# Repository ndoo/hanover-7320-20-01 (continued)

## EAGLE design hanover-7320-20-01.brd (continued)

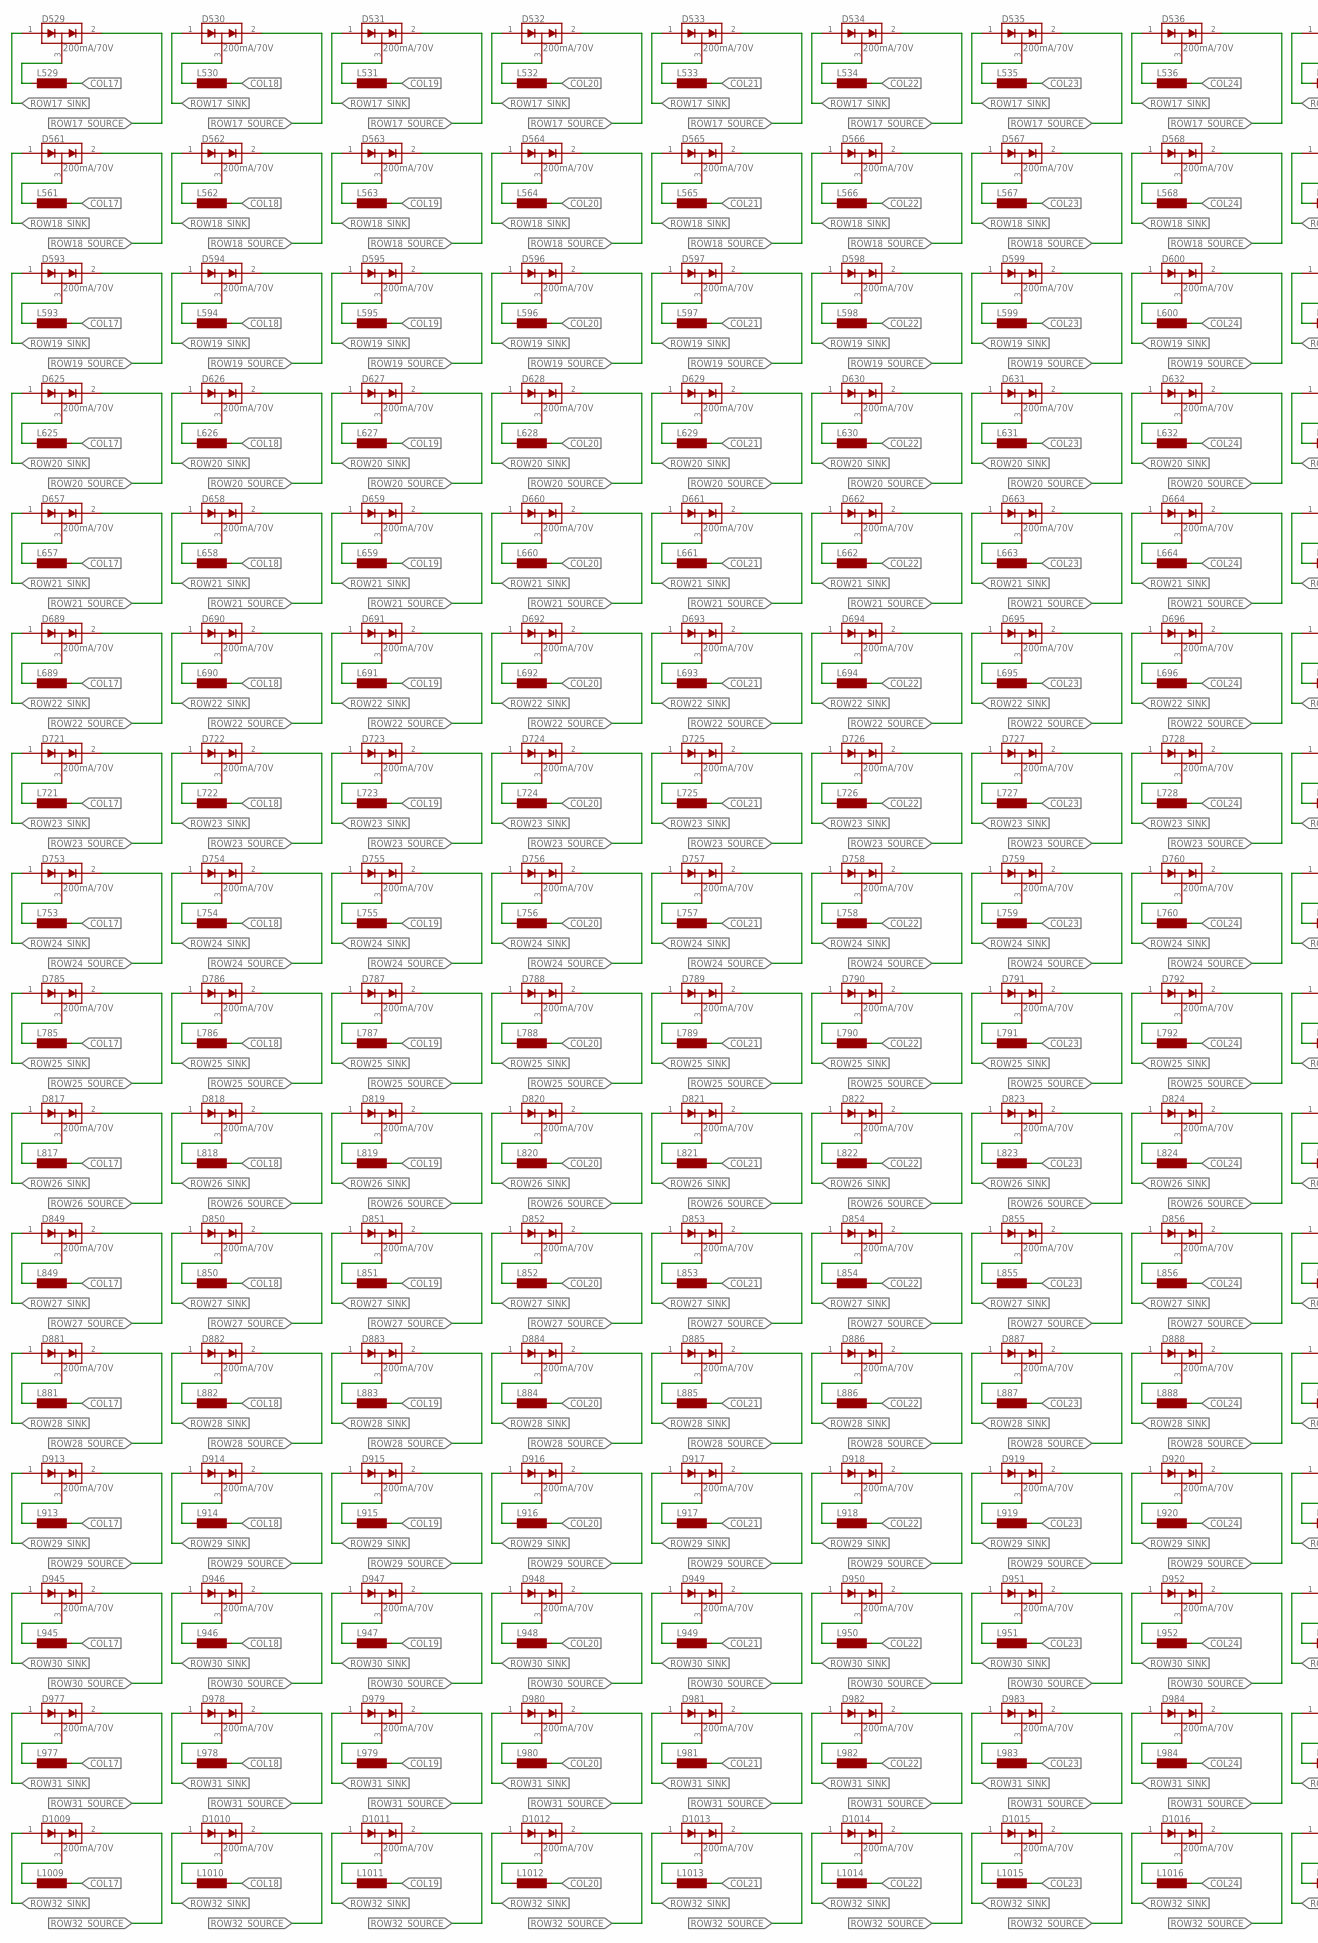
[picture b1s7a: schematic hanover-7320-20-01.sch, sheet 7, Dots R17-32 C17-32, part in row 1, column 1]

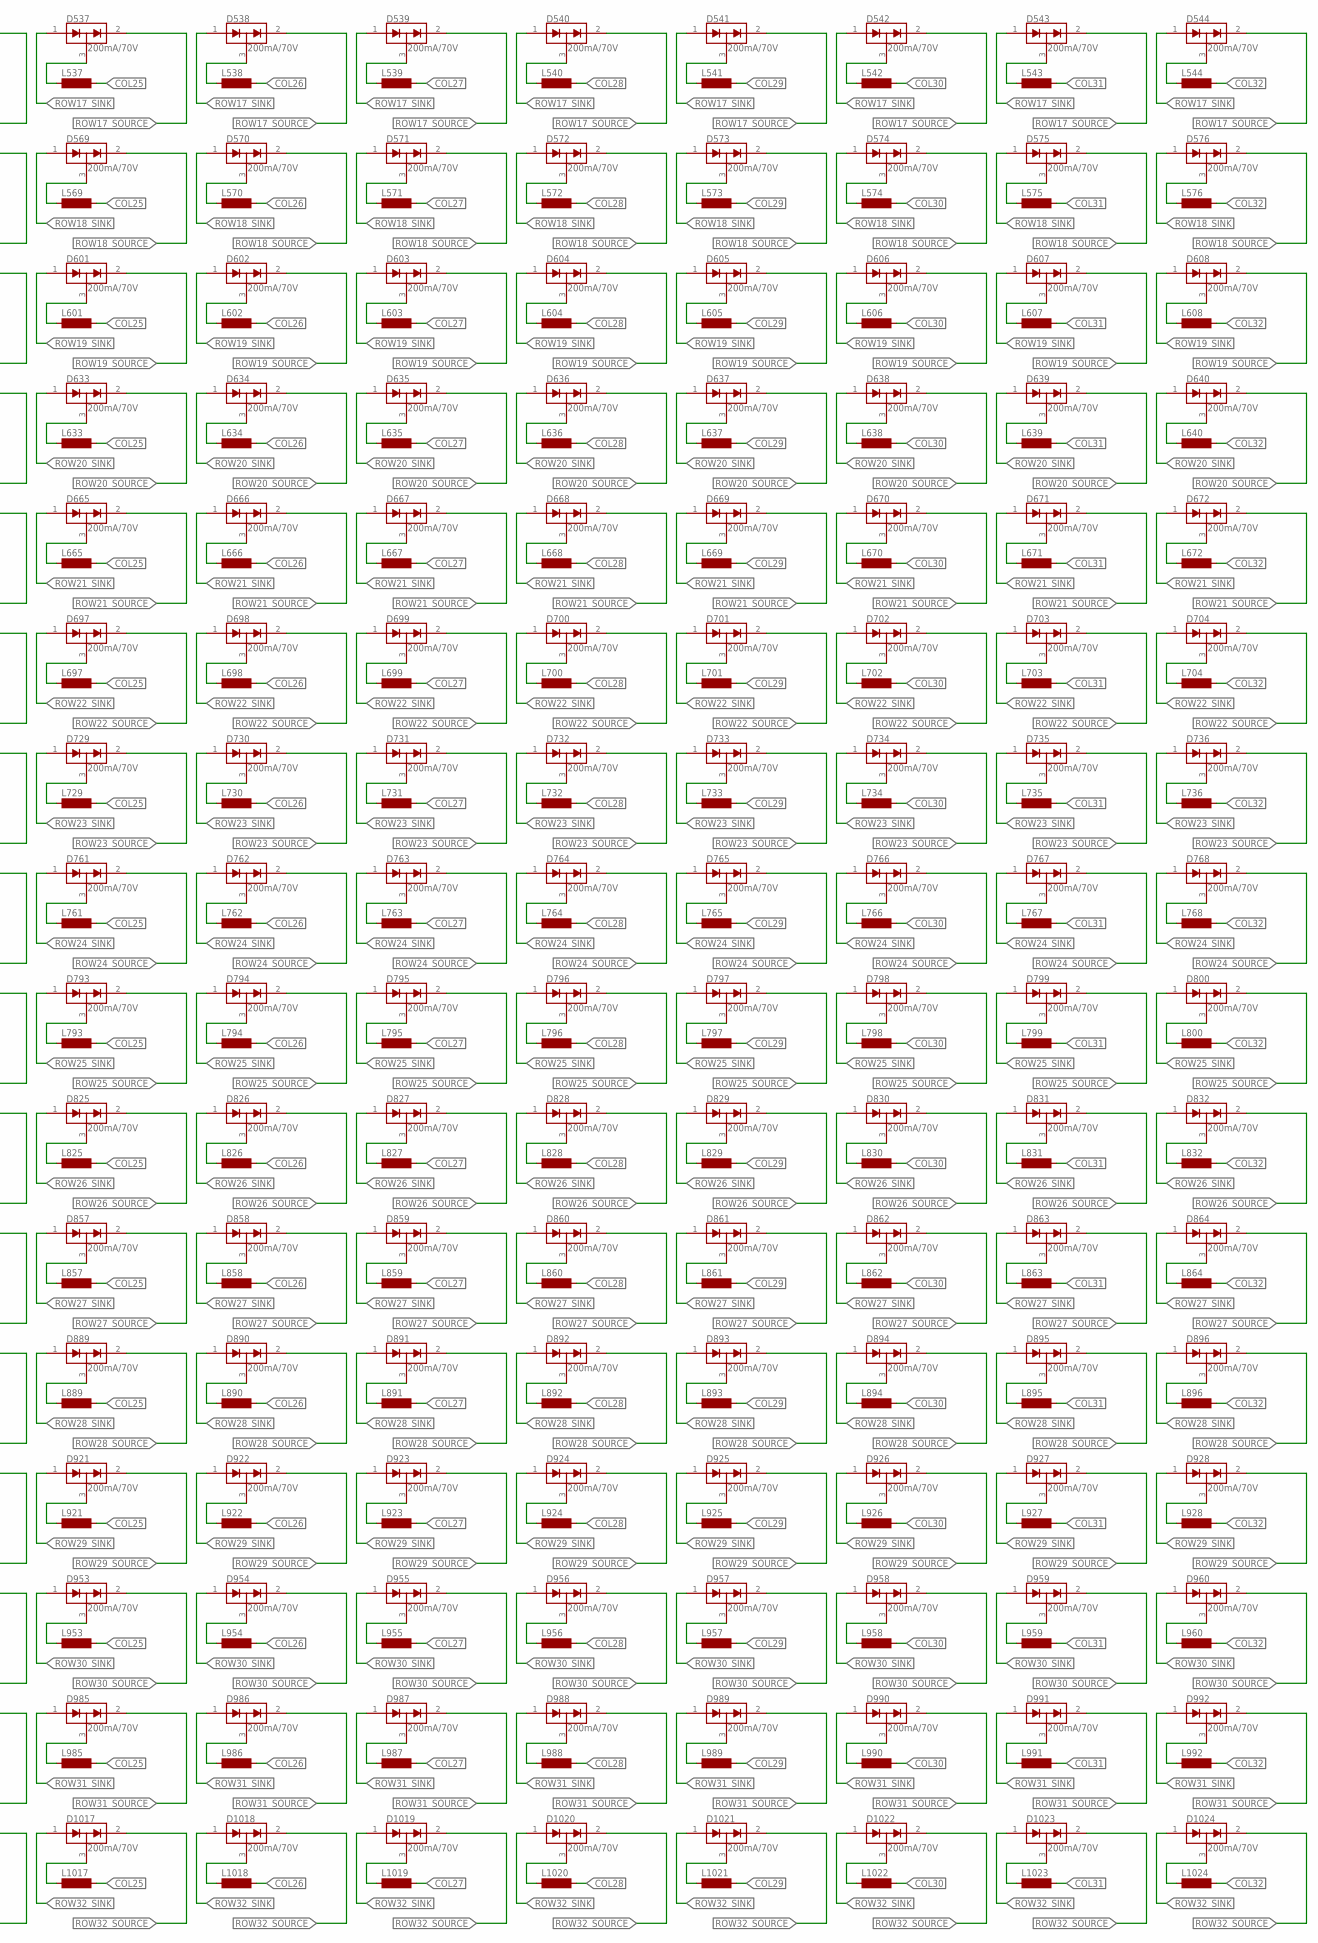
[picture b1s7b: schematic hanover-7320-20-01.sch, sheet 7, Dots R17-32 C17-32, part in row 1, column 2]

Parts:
D529, D530, D531, D532, D533, D534, D535, D536, D537, D538, D539, D540, D541, D542, D543, D544, D561, D562, D563, D564, D565, D566, D567, D568, D569, D570, D571, D572, D573, D574, D575, D576, D593, D594, D595, D596, D597, D598, D599, D600, D601, D602, D603, D604, D605, D606, D607, D608, D625, D626, D627, D628, D629, D630, D631, D632, D633, D634, D635, D636, D637, D638, D639, D640, D657, D658, D659, D660, D661, D662, D663, D664, D665, D666, D667, D668, D669, D670, D671, D672, D689, D690, D691, D692, D693, D694, D695, D696, D697, D698, D699, D700, D701, D702, D703, D704, D721, D722, D723, D724, D725, D726, D727, D728, D729, D730, D731, D732, D733, D734, D735, D736, D753, D754, D755, D756, D757, D758, D759, D760, D761, D762, D763, D764, D765, D766, D767, D768, D785, D786, D787, D788, D789, D790, D791, D792, D793, D794, D795, D796, D797, D798, D799, D800, D817, D818, D819, D820, D821, D822, D823, D824, D825, D826, D827, D828, D829, D830, D831, D832, D849, D850, D851, D852, D853, D854, D855, D856, D857, D858, D859, D860, D861, D862, D863, D864, D881, D882, D883, D884, D885, D886, D887, D888, D889, D890, D891, D892, D893, D894, D895, D896, D913, D914, D915, D916, D917, D918, D919, D920, D921, D922, D923, D924, D925, D926, D927, D928, D945, D946, D947, D948, D949, D950, D951, D952, D953, D954, D955, D956, D957, D958, D959, D960, D977, D978, D979, D980, D981, D982, D983, D984, D985, D986, D987, D988, D989, D990, D991, D992, D1009, D1010, D1011, D1012, D1013, D1014, D1015, D1016, D1017, D1018, D1019, D1020, D1021, D1022, D1023, D1024: 200mA/70V; SOT23-3
L529, L530, L531, L532, L533, L534, L535, L536, L537, L538, L539, L540, L541, L542, L543, L544, L561, L562, L563, L564, L565, L566, L567, L568, L569, L570, L571, L572, L573, L574, L575, L576, L593, L594, L595, L596, L597, L598, L599, L600, L601, L602, L603, L604, L605, L606, L607, L608, L625, L626, L627, L628, L629, L630, L631, L632, L633, L634, L635, L636, L637, L638, L639, L640, L657, L658, L659, L660, L661, L662, L663, L664, L665, L666, L667, L668, L669, L670, L671, L672, L689, L690, L691, L692, L693, L694, L695, L696, L697, L698, L699, L700, L701, L702, L703, L704, L721, L722, L723, L724, L725, L726, L727, L728, L729, L730, L731, L732, L733, L734, L735, L736, L753, L754, L755, L756, L757, L758, L759, L760, L761, L762, L763, L764, L765, L766, L767, L768, L785, L786, L787, L788, L789, L790, L791, L792, L793, L794, L795, L796, L797, L798, L799, L800, L817, L818, L819, L820, L821, L822, L823, L824, L825, L826, L827, L828, L829, L830, L831, L832, L849, L850, L851, L852, L853, L854, L855, L856, L857, L858, L859, L860, L861, L862, L863, L864, L881, L882, L883, L884, L885, L886, L887, L888, L889, L890, L891, L892, L893, L894, L895, L896, L913, L914, L915, L916, L917, L918, L919, L920, L921, L922, L923, L924, L925, L926, L927, L928, L945, L946, L947, L948, L949, L950, L951, L952, L953, L954, L955, L956, L957, L958, L959, L960, L977, L978, L979, L980, L981, L982, L983, L984, L985, L986, L987, L988, L989, L990, L991, L992, L1009, L1010, L1011, L1012, L1013, L1014, L1015, L1016, L1017, L1018, L1019, L1020, L1021, L1022, L1023, L1024: SD8

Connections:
COL17: L529.2, L561.2, L593.2, L625.2, L657.2, L689.2, L721.2, L753.2, L785.2, L817.2, L849.2, L881.2, L913.2, L945.2, L977.2, L1009.2; also elsewhere on the board
COL18: L530.2, L562.2, L594.2, L626.2, L658.2, L690.2, L722.2, L754.2, L786.2, L818.2, L850.2, L882.2, L914.2, L946.2, L978.2, L1010.2; also elsewhere on the board
COL19: L531.2, L563.2, L595.2, L627.2, L659.2, L691.2, L723.2, L755.2, L787.2, L819.2, L851.2, L883.2, L915.2, L947.2, L979.2, L1011.2; also elsewhere on the board
COL20: L532.2, L564.2, L596.2, L628.2, L660.2, L692.2, L724.2, L756.2, L788.2, L820.2, L852.2, L884.2, L916.2, L948.2, L980.2, L1012.2; also elsewhere on the board
COL21: L533.2, L565.2, L597.2, L629.2, L661.2, L693.2, L725.2, L757.2, L789.2, L821.2, L853.2, L885.2, L917.2, L949.2, L981.2, L1013.2; also elsewhere on the board
COL22: L534.2, L566.2, L598.2, L630.2, L662.2, L694.2, L726.2, L758.2, L790.2, L822.2, L854.2, L886.2, L918.2, L950.2, L982.2, L1014.2; also elsewhere on the board
COL23: L535.2, L567.2, L599.2, L631.2, L663.2, L695.2, L727.2, L759.2, L791.2, L823.2, L855.2, L887.2, L919.2, L951.2, L983.2, L1015.2; also elsewhere on the board
COL24: L536.2, L568.2, L600.2, L632.2, L664.2, L696.2, L728.2, L760.2, L792.2, L824.2, L856.2, L888.2, L920.2, L952.2, L984.2, L1016.2; also elsewhere on the board
COL25: L537.2, L569.2, L601.2, L633.2, L665.2, L697.2, L729.2, L761.2, L793.2, L825.2, L857.2, L889.2, L921.2, L953.2, L985.2, L1017.2; also elsewhere on the board
COL26: L538.2, L570.2, L602.2, L634.2, L666.2, L698.2, L730.2, L762.2, L794.2, L826.2, L858.2, L890.2, L922.2, L954.2, L986.2, L1018.2; also elsewhere on the board
COL27: L539.2, L571.2, L603.2, L635.2, L667.2, L699.2, L731.2, L763.2, L795.2, L827.2, L859.2, L891.2, L923.2, L955.2, L987.2, L1019.2; also elsewhere on the board
COL28: L540.2, L572.2, L604.2, L636.2, L668.2, L700.2, L732.2, L764.2, L796.2, L828.2, L860.2, L892.2, L924.2, L956.2, L988.2, L1020.2; also elsewhere on the board
COL29: L541.2, L573.2, L605.2, L637.2, L669.2, L701.2, L733.2, L765.2, L797.2, L829.2, L861.2, L893.2, L925.2, L957.2, L989.2, L1021.2; also elsewhere on the board
COL30: L542.2, L574.2, L606.2, L638.2, L670.2, L702.2, L734.2, L766.2, L798.2, L830.2, L862.2, L894.2, L926.2, L958.2, L990.2, L1022.2; also elsewhere on the board
COL31: L543.2, L575.2, L607.2, L639.2, L671.2, L703.2, L735.2, L767.2, L799.2, L831.2, L863.2, L895.2, L927.2, L959.2, L991.2, L1023.2; also elsewhere on the board
COL32: L544.2, L576.2, L608.2, L640.2, L672.2, L704.2, L736.2, L768.2, L800.2, L832.2, L864.2, L896.2, L928.2, L960.2, L992.2, L1024.2; also elsewhere on the board
unnamed: D529.3 (COM), L529.1
unnamed: D530.3 (COM), L530.1
unnamed: D531.3 (COM), L531.1
unnamed: D532.3 (COM), L532.1
unnamed: D533.3 (COM), L533.1
unnamed: D534.3 (COM), L534.1
unnamed: D535.3 (COM), L535.1
unnamed: D536.3 (COM), L536.1
unnamed: D537.3 (COM), L537.1
unnamed: D538.3 (COM), L538.1
unnamed: D539.3 (COM), L539.1
unnamed: D540.3 (COM), L540.1
unnamed: D541.3 (COM), L541.1
unnamed: D542.3 (COM), L542.1
unnamed: D543.3 (COM), L543.1
unnamed: D544.3 (COM), L544.1
unnamed: D561.3 (COM), L561.1
unnamed: D562.3 (COM), L562.1
unnamed: D563.3 (COM), L563.1
unnamed: D564.3 (COM), L564.1
unnamed: D565.3 (COM), L565.1
unnamed: D566.3 (COM), L566.1
unnamed: D567.3 (COM), L567.1
unnamed: D568.3 (COM), L568.1
unnamed: D569.3 (COM), L569.1
unnamed: D570.3 (COM), L570.1
unnamed: D571.3 (COM), L571.1
unnamed: D572.3 (COM), L572.1
unnamed: D573.3 (COM), L573.1
unnamed: D574.3 (COM), L574.1
unnamed: D575.3 (COM), L575.1
unnamed: D576.3 (COM), L576.1
unnamed: D593.3 (COM), L593.1
unnamed: D594.3 (COM), L594.1
unnamed: D595.3 (COM), L595.1
unnamed: D596.3 (COM), L596.1
unnamed: D597.3 (COM), L597.1
unnamed: D598.3 (COM), L598.1
unnamed: D599.3 (COM), L599.1
unnamed: D600.3 (COM), L600.1
unnamed: D601.3 (COM), L601.1
unnamed: D602.3 (COM), L602.1
unnamed: D603.3 (COM), L603.1
unnamed: D604.3 (COM), L604.1
unnamed: D605.3 (COM), L605.1
unnamed: D606.3 (COM), L606.1
unnamed: D607.3 (COM), L607.1
unnamed: D608.3 (COM), L608.1
unnamed: D625.3 (COM), L625.1
unnamed: D626.3 (COM), L626.1
unnamed: D627.3 (COM), L627.1
unnamed: D628.3 (COM), L628.1
unnamed: D629.3 (COM), L629.1
unnamed: D630.3 (COM), L630.1
unnamed: D631.3 (COM), L631.1
unnamed: D632.3 (COM), L632.1
unnamed: D633.3 (COM), L633.1
unnamed: D634.3 (COM), L634.1
unnamed: D635.3 (COM), L635.1
unnamed: D636.3 (COM), L636.1
unnamed: D637.3 (COM), L637.1
unnamed: D638.3 (COM), L638.1
unnamed: D639.3 (COM), L639.1
unnamed: D640.3 (COM), L640.1
unnamed: D657.3 (COM), L657.1
unnamed: D658.3 (COM), L658.1
unnamed: D659.3 (COM), L659.1
unnamed: D660.3 (COM), L660.1
unnamed: D661.3 (COM), L661.1
unnamed: D662.3 (COM), L662.1
unnamed: D663.3 (COM), L663.1
unnamed: D664.3 (COM), L664.1
unnamed: D665.3 (COM), L665.1
unnamed: D666.3 (COM), L666.1
unnamed: D667.3 (COM), L667.1
unnamed: D668.3 (COM), L668.1
unnamed: D669.3 (COM), L669.1
unnamed: D670.3 (COM), L670.1
unnamed: D671.3 (COM), L671.1
unnamed: D672.3 (COM), L672.1
unnamed: D689.3 (COM), L689.1
unnamed: D690.3 (COM), L690.1
unnamed: D691.3 (COM), L691.1
unnamed: D692.3 (COM), L692.1
unnamed: D693.3 (COM), L693.1
unnamed: D694.3 (COM), L694.1
unnamed: D695.3 (COM), L695.1
unnamed: D696.3 (COM), L696.1
unnamed: D697.3 (COM), L697.1
unnamed: D698.3 (COM), L698.1
unnamed: D699.3 (COM), L699.1
unnamed: D700.3 (COM), L700.1
unnamed: D701.3 (COM), L701.1
unnamed: D702.3 (COM), L702.1
unnamed: D703.3 (COM), L703.1
unnamed: D704.3 (COM), L704.1
unnamed: D721.3 (COM), L721.1
unnamed: D722.3 (COM), L722.1
unnamed: D723.3 (COM), L723.1
unnamed: D724.3 (COM), L724.1
unnamed: D725.3 (COM), L725.1
unnamed: D726.3 (COM), L726.1
unnamed: D727.3 (COM), L727.1
unnamed: D728.3 (COM), L728.1
unnamed: D729.3 (COM), L729.1
unnamed: D730.3 (COM), L730.1
unnamed: D731.3 (COM), L731.1
unnamed: D732.3 (COM), L732.1
unnamed: D733.3 (COM), L733.1
unnamed: D734.3 (COM), L734.1
unnamed: D735.3 (COM), L735.1
unnamed: D736.3 (COM), L736.1
unnamed: D753.3 (COM), L753.1
unnamed: D754.3 (COM), L754.1
unnamed: D755.3 (COM), L755.1
unnamed: D756.3 (COM), L756.1
unnamed: D757.3 (COM), L757.1
unnamed: D758.3 (COM), L758.1
unnamed: D759.3 (COM), L759.1
unnamed: D760.3 (COM), L760.1
unnamed: D761.3 (COM), L761.1
unnamed: D762.3 (COM), L762.1
unnamed: D763.3 (COM), L763.1
unnamed: D764.3 (COM), L764.1
unnamed: D765.3 (COM), L765.1
unnamed: D766.3 (COM), L766.1
unnamed: D767.3 (COM), L767.1
unnamed: D768.3 (COM), L768.1
unnamed: D785.3 (COM), L785.1
unnamed: D786.3 (COM), L786.1
unnamed: D787.3 (COM), L787.1
unnamed: D788.3 (COM), L788.1
unnamed: D789.3 (COM), L789.1
unnamed: D790.3 (COM), L790.1
unnamed: D791.3 (COM), L791.1
unnamed: D792.3 (COM), L792.1
unnamed: D793.3 (COM), L793.1
unnamed: D794.3 (COM), L794.1
unnamed: D795.3 (COM), L795.1
unnamed: D796.3 (COM), L796.1
unnamed: D797.3 (COM), L797.1
unnamed: D798.3 (COM), L798.1
unnamed: D799.3 (COM), L799.1
unnamed: D800.3 (COM), L800.1
unnamed: D817.3 (COM), L817.1
unnamed: D818.3 (COM), L818.1
unnamed: D819.3 (COM), L819.1
unnamed: D820.3 (COM), L820.1
unnamed: D821.3 (COM), L821.1
unnamed: D822.3 (COM), L822.1
unnamed: D823.3 (COM), L823.1
unnamed: D824.3 (COM), L824.1
unnamed: D825.3 (COM), L825.1
unnamed: D826.3 (COM), L826.1
unnamed: D827.3 (COM), L827.1
unnamed: D828.3 (COM), L828.1
unnamed: D829.3 (COM), L829.1
unnamed: D830.3 (COM), L830.1
unnamed: D831.3 (COM), L831.1
unnamed: D832.3 (COM), L832.1
unnamed: D849.3 (COM), L849.1
unnamed: D850.3 (COM), L850.1
unnamed: D851.3 (COM), L851.1
unnamed: D852.3 (COM), L852.1
unnamed: D853.3 (COM), L853.1
unnamed: D854.3 (COM), L854.1
unnamed: D855.3 (COM), L855.1
unnamed: D856.3 (COM), L856.1
unnamed: D857.3 (COM), L857.1
unnamed: D858.3 (COM), L858.1
unnamed: D859.3 (COM), L859.1
unnamed: D860.3 (COM), L860.1
unnamed: D861.3 (COM), L861.1
unnamed: D862.3 (COM), L862.1
unnamed: D863.3 (COM), L863.1
unnamed: D864.3 (COM), L864.1
unnamed: D881.3 (COM), L881.1
unnamed: D882.3 (COM), L882.1
unnamed: D883.3 (COM), L883.1
unnamed: D884.3 (COM), L884.1
unnamed: D885.3 (COM), L885.1
unnamed: D886.3 (COM), L886.1
unnamed: D887.3 (COM), L887.1
unnamed: D888.3 (COM), L888.1
unnamed: D889.3 (COM), L889.1
unnamed: D890.3 (COM), L890.1
unnamed: D891.3 (COM), L891.1
unnamed: D892.3 (COM), L892.1
unnamed: D893.3 (COM), L893.1
unnamed: D894.3 (COM), L894.1
unnamed: D895.3 (COM), L895.1
unnamed: D896.3 (COM), L896.1
unnamed: D913.3 (COM), L913.1
unnamed: D914.3 (COM), L914.1
unnamed: D915.3 (COM), L915.1
unnamed: D916.3 (COM), L916.1
unnamed: D917.3 (COM), L917.1
unnamed: D918.3 (COM), L918.1
unnamed: D919.3 (COM), L919.1
unnamed: D920.3 (COM), L920.1
unnamed: D921.3 (COM), L921.1
unnamed: D922.3 (COM), L922.1
unnamed: D923.3 (COM), L923.1
unnamed: D924.3 (COM), L924.1
unnamed: D925.3 (COM), L925.1
unnamed: D926.3 (COM), L926.1
unnamed: D927.3 (COM), L927.1
unnamed: D928.3 (COM), L928.1
unnamed: D945.3 (COM), L945.1
unnamed: D946.3 (COM), L946.1
unnamed: D947.3 (COM), L947.1
unnamed: D948.3 (COM), L948.1
unnamed: D949.3 (COM), L949.1
unnamed: D950.3 (COM), L950.1
unnamed: D951.3 (COM), L951.1
unnamed: D952.3 (COM), L952.1
unnamed: D953.3 (COM), L953.1
unnamed: D954.3 (COM), L954.1
unnamed: D955.3 (COM), L955.1
unnamed: D956.3 (COM), L956.1
unnamed: D957.3 (COM), L957.1
unnamed: D958.3 (COM), L958.1
unnamed: D959.3 (COM), L959.1
unnamed: D960.3 (COM), L960.1
unnamed: D977.3 (COM), L977.1
unnamed: D978.3 (COM), L978.1
unnamed: D979.3 (COM), L979.1
unnamed: D980.3 (COM), L980.1
unnamed: D981.3 (COM), L981.1
unnamed: D982.3 (COM), L982.1
unnamed: D983.3 (COM), L983.1
unnamed: D984.3 (COM), L984.1
unnamed: D985.3 (COM), L985.1
unnamed: D986.3 (COM), L986.1
unnamed: D987.3 (COM), L987.1
unnamed: D988.3 (COM), L988.1
unnamed: D989.3 (COM), L989.1
unnamed: D990.3 (COM), L990.1
unnamed: D991.3 (COM), L991.1
unnamed: D992.3 (COM), L992.1
unnamed: D1009.3 (COM), L1009.1
unnamed: D1010.3 (COM), L1010.1
unnamed: D1011.3 (COM), L1011.1
unnamed: D1012.3 (COM), L1012.1
unnamed: D1013.3 (COM), L1013.1
unnamed: D1014.3 (COM), L1014.1
unnamed: D1015.3 (COM), L1015.1
unnamed: D1016.3 (COM), L1016.1
unnamed: D1017.3 (COM), L1017.1
unnamed: D1018.3 (COM), L1018.1
unnamed: D1019.3 (COM), L1019.1
unnamed: D1020.3 (COM), L1020.1
unnamed: D1021.3 (COM), L1021.1
unnamed: D1022.3 (COM), L1022.1
unnamed: D1023.3 (COM), L1023.1
unnamed: D1024.3 (COM), L1024.1
ROW17_SINK: D529.1 (A1), D530.1 (A1), D531.1 (A1), D532.1 (A1), D533.1 (A1), D534.1 (A1), D535.1 (A1), D536.1 (A1), D537.1 (A1), D538.1 (A1), D539.1 (A1), D540.1 (A1), D541.1 (A1), D542.1 (A1), D543.1 (A1), D544.1 (A1); also elsewhere on the board
ROW17_SOURCE: D529.2 (C2), D530.2 (C2), D531.2 (C2), D532.2 (C2), D533.2 (C2), D534.2 (C2), D535.2 (C2), D536.2 (C2), D537.2 (C2), D538.2 (C2), D539.2 (C2), D540.2 (C2), D541.2 (C2), D542.2 (C2), D543.2 (C2), D544.2 (C2); also elsewhere on the board
ROW18_SINK: D561.1 (A1), D562.1 (A1), D563.1 (A1), D564.1 (A1), D565.1 (A1), D566.1 (A1), D567.1 (A1), D568.1 (A1), D569.1 (A1), D570.1 (A1), D571.1 (A1), D572.1 (A1), D573.1 (A1), D574.1 (A1), D575.1 (A1), D576.1 (A1); also elsewhere on the board
ROW18_SOURCE: D561.2 (C2), D562.2 (C2), D563.2 (C2), D564.2 (C2), D565.2 (C2), D566.2 (C2), D567.2 (C2), D568.2 (C2), D569.2 (C2), D570.2 (C2), D571.2 (C2), D572.2 (C2), D573.2 (C2), D574.2 (C2), D575.2 (C2), D576.2 (C2); also elsewhere on the board
ROW19_SINK: D593.1 (A1), D594.1 (A1), D595.1 (A1), D596.1 (A1), D597.1 (A1), D598.1 (A1), D599.1 (A1), D600.1 (A1), D601.1 (A1), D602.1 (A1), D603.1 (A1), D604.1 (A1), D605.1 (A1), D606.1 (A1), D607.1 (A1), D608.1 (A1); also elsewhere on the board
ROW19_SOURCE: D593.2 (C2), D594.2 (C2), D595.2 (C2), D596.2 (C2), D597.2 (C2), D598.2 (C2), D599.2 (C2), D600.2 (C2), D601.2 (C2), D602.2 (C2), D603.2 (C2), D604.2 (C2), D605.2 (C2), D606.2 (C2), D607.2 (C2), D608.2 (C2); also elsewhere on the board
ROW20_SINK: D625.1 (A1), D626.1 (A1), D627.1 (A1), D628.1 (A1), D629.1 (A1), D630.1 (A1), D631.1 (A1), D632.1 (A1), D633.1 (A1), D634.1 (A1), D635.1 (A1), D636.1 (A1), D637.1 (A1), D638.1 (A1), D639.1 (A1), D640.1 (A1); also elsewhere on the board
ROW20_SOURCE: D625.2 (C2), D626.2 (C2), D627.2 (C2), D628.2 (C2), D629.2 (C2), D630.2 (C2), D631.2 (C2), D632.2 (C2), D633.2 (C2), D634.2 (C2), D635.2 (C2), D636.2 (C2), D637.2 (C2), D638.2 (C2), D639.2 (C2), D640.2 (C2); also elsewhere on the board
ROW21_SINK: D657.1 (A1), D658.1 (A1), D659.1 (A1), D660.1 (A1), D661.1 (A1), D662.1 (A1), D663.1 (A1), D664.1 (A1), D665.1 (A1), D666.1 (A1), D667.1 (A1), D668.1 (A1), D669.1 (A1), D670.1 (A1), D671.1 (A1), D672.1 (A1); also elsewhere on the board
ROW21_SOURCE: D657.2 (C2), D658.2 (C2), D659.2 (C2), D660.2 (C2), D661.2 (C2), D662.2 (C2), D663.2 (C2), D664.2 (C2), D665.2 (C2), D666.2 (C2), D667.2 (C2), D668.2 (C2), D669.2 (C2), D670.2 (C2), D671.2 (C2), D672.2 (C2); also elsewhere on the board
ROW22_SINK: D689.1 (A1), D690.1 (A1), D691.1 (A1), D692.1 (A1), D693.1 (A1), D694.1 (A1), D695.1 (A1), D696.1 (A1), D697.1 (A1), D698.1 (A1), D699.1 (A1), D700.1 (A1), D701.1 (A1), D702.1 (A1), D703.1 (A1), D704.1 (A1); also elsewhere on the board
ROW22_SOURCE: D689.2 (C2), D690.2 (C2), D691.2 (C2), D692.2 (C2), D693.2 (C2), D694.2 (C2), D695.2 (C2), D696.2 (C2), D697.2 (C2), D698.2 (C2), D699.2 (C2), D700.2 (C2), D701.2 (C2), D702.2 (C2), D703.2 (C2), D704.2 (C2); also elsewhere on the board
ROW23_SINK: D721.1 (A1), D722.1 (A1), D723.1 (A1), D724.1 (A1), D725.1 (A1), D726.1 (A1), D727.1 (A1), D728.1 (A1), D729.1 (A1), D730.1 (A1), D731.1 (A1), D732.1 (A1), D733.1 (A1), D734.1 (A1), D735.1 (A1), D736.1 (A1); also elsewhere on the board
ROW23_SOURCE: D721.2 (C2), D722.2 (C2), D723.2 (C2), D724.2 (C2), D725.2 (C2), D726.2 (C2), D727.2 (C2), D728.2 (C2), D729.2 (C2), D730.2 (C2), D731.2 (C2), D732.2 (C2), D733.2 (C2), D734.2 (C2), D735.2 (C2), D736.2 (C2); also elsewhere on the board
ROW24_SINK: D753.1 (A1), D754.1 (A1), D755.1 (A1), D756.1 (A1), D757.1 (A1), D758.1 (A1), D759.1 (A1), D760.1 (A1), D761.1 (A1), D762.1 (A1), D763.1 (A1), D764.1 (A1), D765.1 (A1), D766.1 (A1), D767.1 (A1), D768.1 (A1); also elsewhere on the board
ROW24_SOURCE: D753.2 (C2), D754.2 (C2), D755.2 (C2), D756.2 (C2), D757.2 (C2), D758.2 (C2), D759.2 (C2), D760.2 (C2), D761.2 (C2), D762.2 (C2), D763.2 (C2), D764.2 (C2), D765.2 (C2), D766.2 (C2), D767.2 (C2), D768.2 (C2); also elsewhere on the board
ROW25_SINK: D785.1 (A1), D786.1 (A1), D787.1 (A1), D788.1 (A1), D789.1 (A1), D790.1 (A1), D791.1 (A1), D792.1 (A1), D793.1 (A1), D794.1 (A1), D795.1 (A1), D796.1 (A1), D797.1 (A1), D798.1 (A1), D799.1 (A1), D800.1 (A1); also elsewhere on the board
ROW25_SOURCE: D785.2 (C2), D786.2 (C2), D787.2 (C2), D788.2 (C2), D789.2 (C2), D790.2 (C2), D791.2 (C2), D792.2 (C2), D793.2 (C2), D794.2 (C2), D795.2 (C2), D796.2 (C2), D797.2 (C2), D798.2 (C2), D799.2 (C2), D800.2 (C2); also elsewhere on the board
ROW26_SINK: D817.1 (A1), D818.1 (A1), D819.1 (A1), D820.1 (A1), D821.1 (A1), D822.1 (A1), D823.1 (A1), D824.1 (A1), D825.1 (A1), D826.1 (A1), D827.1 (A1), D828.1 (A1), D829.1 (A1), D830.1 (A1), D831.1 (A1), D832.1 (A1); also elsewhere on the board
ROW26_SOURCE: D817.2 (C2), D818.2 (C2), D819.2 (C2), D820.2 (C2), D821.2 (C2), D822.2 (C2), D823.2 (C2), D824.2 (C2), D825.2 (C2), D826.2 (C2), D827.2 (C2), D828.2 (C2), D829.2 (C2), D830.2 (C2), D831.2 (C2), D832.2 (C2); also elsewhere on the board
ROW27_SINK: D849.1 (A1), D850.1 (A1), D851.1 (A1), D852.1 (A1), D853.1 (A1), D854.1 (A1), D855.1 (A1), D856.1 (A1), D857.1 (A1), D858.1 (A1), D859.1 (A1), D860.1 (A1), D861.1 (A1), D862.1 (A1), D863.1 (A1), D864.1 (A1); also elsewhere on the board
ROW27_SOURCE: D849.2 (C2), D850.2 (C2), D851.2 (C2), D852.2 (C2), D853.2 (C2), D854.2 (C2), D855.2 (C2), D856.2 (C2), D857.2 (C2), D858.2 (C2), D859.2 (C2), D860.2 (C2), D861.2 (C2), D862.2 (C2), D863.2 (C2), D864.2 (C2); also elsewhere on the board
ROW28_SINK: D881.1 (A1), D882.1 (A1), D883.1 (A1), D884.1 (A1), D885.1 (A1), D886.1 (A1), D887.1 (A1), D888.1 (A1), D889.1 (A1), D890.1 (A1), D891.1 (A1), D892.1 (A1), D893.1 (A1), D894.1 (A1), D895.1 (A1), D896.1 (A1); also elsewhere on the board
ROW28_SOURCE: D881.2 (C2), D882.2 (C2), D883.2 (C2), D884.2 (C2), D885.2 (C2), D886.2 (C2), D887.2 (C2), D888.2 (C2), D889.2 (C2), D890.2 (C2), D891.2 (C2), D892.2 (C2), D893.2 (C2), D894.2 (C2), D895.2 (C2), D896.2 (C2); also elsewhere on the board
ROW29_SINK: D913.1 (A1), D914.1 (A1), D915.1 (A1), D916.1 (A1), D917.1 (A1), D918.1 (A1), D919.1 (A1), D920.1 (A1), D921.1 (A1), D922.1 (A1), D923.1 (A1), D924.1 (A1), D925.1 (A1), D926.1 (A1), D927.1 (A1), D928.1 (A1); also elsewhere on the board
ROW29_SOURCE: D913.2 (C2), D914.2 (C2), D915.2 (C2), D916.2 (C2), D917.2 (C2), D918.2 (C2), D919.2 (C2), D920.2 (C2), D921.2 (C2), D922.2 (C2), D923.2 (C2), D924.2 (C2), D925.2 (C2), D926.2 (C2), D927.2 (C2), D928.2 (C2); also elsewhere on the board
ROW30_SINK: D945.1 (A1), D946.1 (A1), D947.1 (A1), D948.1 (A1), D949.1 (A1), D950.1 (A1), D951.1 (A1), D952.1 (A1), D953.1 (A1), D954.1 (A1), D955.1 (A1), D956.1 (A1), D957.1 (A1), D958.1 (A1), D959.1 (A1), D960.1 (A1); also elsewhere on the board
ROW30_SOURCE: D945.2 (C2), D946.2 (C2), D947.2 (C2), D948.2 (C2), D949.2 (C2), D950.2 (C2), D951.2 (C2), D952.2 (C2), D953.2 (C2), D954.2 (C2), D955.2 (C2), D956.2 (C2), D957.2 (C2), D958.2 (C2), D959.2 (C2), D960.2 (C2); also elsewhere on the board
ROW31_SINK: D977.1 (A1), D978.1 (A1), D979.1 (A1), D980.1 (A1), D981.1 (A1), D982.1 (A1), D983.1 (A1), D984.1 (A1), D985.1 (A1), D986.1 (A1), D987.1 (A1), D988.1 (A1), D989.1 (A1), D990.1 (A1), D991.1 (A1), D992.1 (A1); also elsewhere on the board
ROW31_SOURCE: D977.2 (C2), D978.2 (C2), D979.2 (C2), D980.2 (C2), D981.2 (C2), D982.2 (C2), D983.2 (C2), D984.2 (C2), D985.2 (C2), D986.2 (C2), D987.2 (C2), D988.2 (C2), D989.2 (C2), D990.2 (C2), D991.2 (C2), D992.2 (C2); also elsewhere on the board
ROW32_SINK: D1009.1 (A1), D1010.1 (A1), D1011.1 (A1), D1012.1 (A1), D1013.1 (A1), D1014.1 (A1), D1015.1 (A1), D1016.1 (A1), D1017.1 (A1), D1018.1 (A1), D1019.1 (A1), D1020.1 (A1), D1021.1 (A1), D1022.1 (A1), D1023.1 (A1), D1024.1 (A1); also elsewhere on the board
ROW32_SOURCE: D1009.2 (C2), D1010.2 (C2), D1011.2 (C2), D1012.2 (C2), D1013.2 (C2), D1014.2 (C2), D1015.2 (C2), D1016.2 (C2), D1017.2 (C2), D1018.2 (C2), D1019.2 (C2), D1020.2 (C2), D1021.2 (C2), D1022.2 (C2), D1023.2 (C2), D1024.2 (C2); also elsewhere on the board

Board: 2 copper layers, 2078 parts (0 on the bottom side), 1283 nets, no tracks yet.

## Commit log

2020-05-09 Add initial (incomplete) tracing work
2020-05-11 Populate diodes and coils
    The coils are not the actual dots and are just placeholders until a library is created for the dots
2020-05-11 Wired transistor arrays to correct 18V lines, separated diodes/coils schematic into 4 sheets, add frames
